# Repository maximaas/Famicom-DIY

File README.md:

# Famicom-DIY

My DIY work on Nintendo Famicom

## Controllers

### Convert FC controllers to adapt to 9-pin RS232 socket
The original FC controller have a 5-pin(1p) or 6-pin(2p) pin head plugged into the socket on main PCB board. Unlike its successors, the FC controller can not be replaced easily without opening the case.

One day a guy claimed that he had successfully designed and made a famiclone named "RGB-FC" which can output through RGBhv or VGA with splendid video quality. So I bought one.

RGB-FC provides two 9-pin controller connectors, can be used with a large number of "Subor" pads. But the pads are sucks, so I have to mod my original controllers to adapt with RGB-FC. 

First, I purchased several RS232 female connectors, then cut the pin head of the controller and started to wire them together.

The wiring method is showed above. The 2p controller has an additional mic wire than the 1p's. I don't know how to wire it so I left it lifted.

Solder the corresponding wires, and assemble the connector.

Enjoy!

## Reproductions

Refer to [https://maximaas.github.io/blog](https://maximaas.github.io/blog) for details.

*   kazzo_scripts: kazzo scripts for certain mappers that anago releases didn't provide or the original one doesn't work well.
*   MMC1 - SLROM.txt: wiring instruction for mmc1 slrom.
*   MMC5 - ETROM.txt: wiring instruction for mmc5 etrom.
*   Namcot-163.txt: wiring instruction for Namcot-163 board.
*   Taito X1-005.txt: wiring instruction for Taito X1-005 board.

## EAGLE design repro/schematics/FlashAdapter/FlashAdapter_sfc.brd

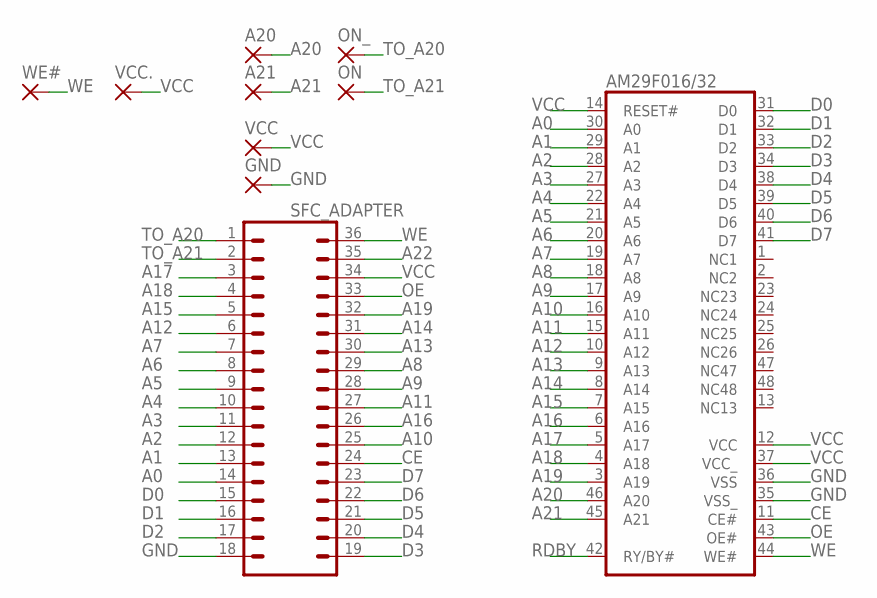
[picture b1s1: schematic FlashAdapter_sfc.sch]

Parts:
A20, A21: SMD2; SMD1,27-2,54
AM29F016/32: AM29F016; TSOP48
GND: SMD2; SMD1,27-2,54
ON: SMD2; SMD1,27-2,54
ON_: SMD2; SMD1,27-2,54
SFC_ADAPTER: DIP36PTH; DIP36
VCC, VCC.: SMD2; SMD1,27-2,54
WE#: SMD2; SMD1,27-2,54

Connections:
A0: AM29F016/32.30 (A0), SFC_ADAPTER.14
A1: AM29F016/32.29 (A1), SFC_ADAPTER.13
A2: AM29F016/32.28 (A2), SFC_ADAPTER.12
A3: AM29F016/32.27 (A3), SFC_ADAPTER.11
A4: AM29F016/32.22 (A4), SFC_ADAPTER.10
A5: AM29F016/32.21 (A5), SFC_ADAPTER.9
A6: AM29F016/32.20 (A6), SFC_ADAPTER.8
A7: AM29F016/32.19 (A7), SFC_ADAPTER.7
A8: AM29F016/32.18 (A8), SFC_ADAPTER.29
A9: AM29F016/32.17 (A9), SFC_ADAPTER.28
A10: AM29F016/32.16 (A10), SFC_ADAPTER.25
A11: AM29F016/32.15 (A11), SFC_ADAPTER.27
A12: AM29F016/32.10 (A12), SFC_ADAPTER.6
A13: AM29F016/32.9 (A13), SFC_ADAPTER.30
A14: AM29F016/32.8 (A14), SFC_ADAPTER.31
A15: AM29F016/32.7 (A15), SFC_ADAPTER.5
A16: AM29F016/32.6 (A16), SFC_ADAPTER.26
A17: AM29F016/32.5 (A17), SFC_ADAPTER.3
A18: AM29F016/32.4 (A18), SFC_ADAPTER.4
A19: AM29F016/32.3 (A19), SFC_ADAPTER.32
A20: A20.1, AM29F016/32.46 (A20)
A21: A21.1, AM29F016/32.45 (A21)
A22: SFC_ADAPTER.35
CE: AM29F016/32.11 (CE#), SFC_ADAPTER.24
D0: AM29F016/32.31 (D0), SFC_ADAPTER.15
D1: AM29F016/32.32 (D1), SFC_ADAPTER.16
D2: AM29F016/32.33 (D2), SFC_ADAPTER.17
D3: AM29F016/32.34 (D3), SFC_ADAPTER.19
D4: AM29F016/32.38 (D4), SFC_ADAPTER.20
D5: AM29F016/32.39 (D5), SFC_ADAPTER.21
D6: AM29F016/32.40 (D6), SFC_ADAPTER.22
D7: AM29F016/32.41 (D7), SFC_ADAPTER.23
GND: AM29F016/32.35 (VSS_), AM29F016/32.36 (VSS), GND.1, SFC_ADAPTER.18
OE: AM29F016/32.43 (OE#), SFC_ADAPTER.33
RDBY: AM29F016/32.42 (RY/BY#)
TO_A20: ON_.1, SFC_ADAPTER.1
TO_A21: ON.1, SFC_ADAPTER.2
VCC: AM29F016/32.12 (VCC), AM29F016/32.14 (RESET#), AM29F016/32.37 (VCC_), SFC_ADAPTER.34, VCC.1, VCC..1
WE: AM29F016/32.44 (WE#), SFC_ADAPTER.36, WE#.1

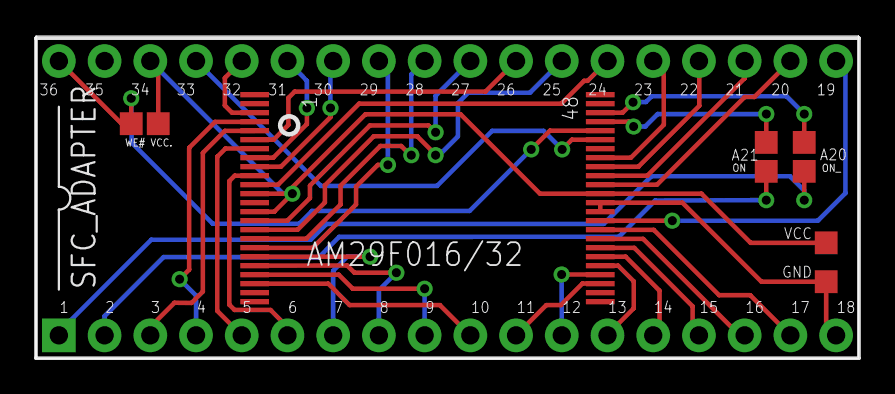
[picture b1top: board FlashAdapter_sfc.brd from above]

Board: 2 copper layers, 45.7 x 17.9 mm, 10 parts (0 on the bottom side), 37 nets.

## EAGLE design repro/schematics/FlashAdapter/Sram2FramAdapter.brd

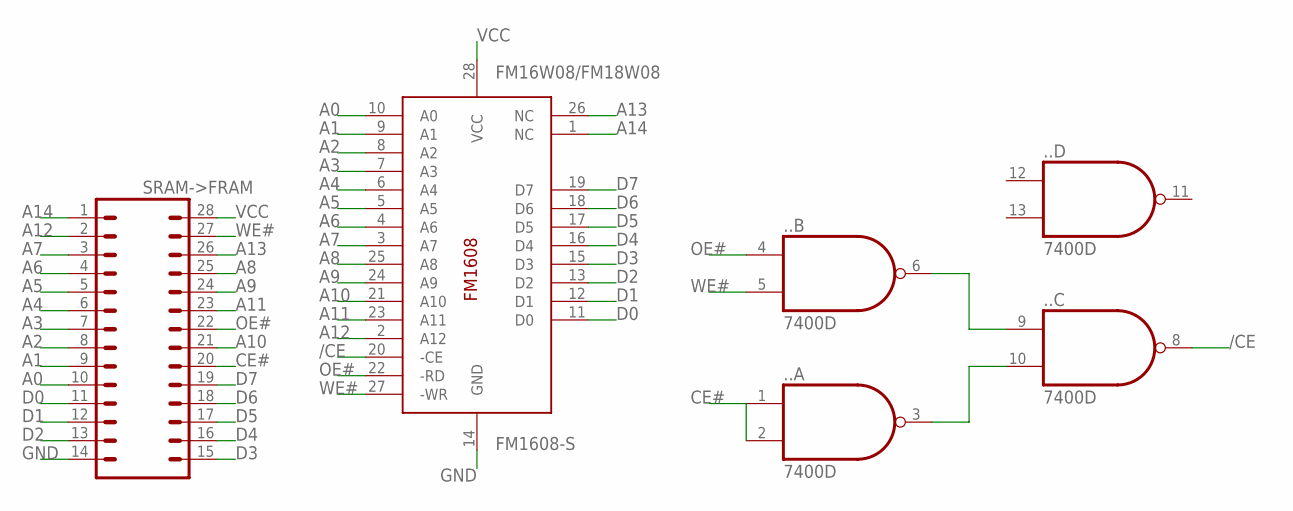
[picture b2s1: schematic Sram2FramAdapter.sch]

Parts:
..: 7400D; SO14
FM16W08/FM18W08: FM1608-S; SO-28W
SRAM->FRAM: DIP28PTH; DIP28

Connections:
/CE: ...8 (O), FM16W08/FM18W08.20 (-CE)
A0: FM16W08/FM18W08.10 (A0), SRAM->FRAM.10
A1: FM16W08/FM18W08.9 (A1), SRAM->FRAM.9
A2: FM16W08/FM18W08.8 (A2), SRAM->FRAM.8
A3: FM16W08/FM18W08.7 (A3), SRAM->FRAM.7
A4: FM16W08/FM18W08.6 (A4), SRAM->FRAM.6
A5: FM16W08/FM18W08.5 (A5), SRAM->FRAM.5
A6: FM16W08/FM18W08.4 (A6), SRAM->FRAM.4
A7: FM16W08/FM18W08.3 (A7), SRAM->FRAM.3
A8: FM16W08/FM18W08.25 (A8), SRAM->FRAM.25
A9: FM16W08/FM18W08.24 (A9), SRAM->FRAM.24
A10: FM16W08/FM18W08.21 (A10), SRAM->FRAM.21
A11: FM16W08/FM18W08.23 (A11), SRAM->FRAM.23
A12: FM16W08/FM18W08.2 (A12), SRAM->FRAM.2
A13: FM16W08/FM18W08.26 (NC), SRAM->FRAM.26
A14: FM16W08/FM18W08.1 (NC), SRAM->FRAM.1
CE#: ...1 (I0), ...2 (I1), SRAM->FRAM.20
D0: FM16W08/FM18W08.11 (D0), SRAM->FRAM.11
D1: FM16W08/FM18W08.12 (D1), SRAM->FRAM.12
D2: FM16W08/FM18W08.13 (D2), SRAM->FRAM.13
D3: FM16W08/FM18W08.15 (D3), SRAM->FRAM.15
D4: FM16W08/FM18W08.16 (D4), SRAM->FRAM.16
D5: FM16W08/FM18W08.17 (D5), SRAM->FRAM.17
D6: FM16W08/FM18W08.18 (D6), SRAM->FRAM.18
D7: FM16W08/FM18W08.19 (D7), SRAM->FRAM.19
GND: ...7 (GND), FM16W08/FM18W08.14 (GND), SRAM->FRAM.14
unnamed: ...6 (O), ...9 (I0)
unnamed: ...3 (O), ...10 (I1)
OE#: ...4 (I0), FM16W08/FM18W08.22 (-RD), SRAM->FRAM.22
VCC: ...14 (VCC), FM16W08/FM18W08.28 (VCC), SRAM->FRAM.28
WE#: ...5 (I1), FM16W08/FM18W08.27 (-WR), SRAM->FRAM.27

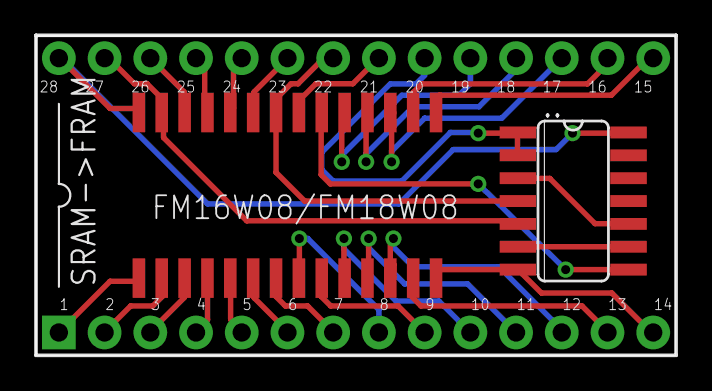
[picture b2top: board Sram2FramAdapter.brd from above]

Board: 2 copper layers, 35.5 x 17.7 mm, 3 parts (0 on the bottom side), 31 nets.

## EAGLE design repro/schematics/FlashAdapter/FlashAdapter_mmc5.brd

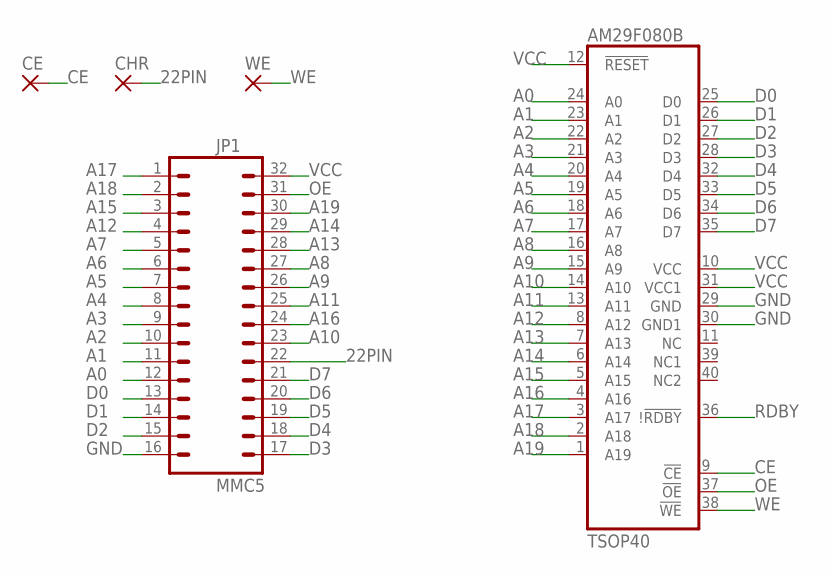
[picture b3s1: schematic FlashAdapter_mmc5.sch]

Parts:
AM29F080B: TSOP40
CE: SMD2; SMD1,27-2,54
CHR: SMD2; SMD1,27-2,54
JP1: MMC5; DIP32
WE: SMD2; SMD1,27-2,54

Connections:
22PIN: CHR.1, JP1.22
A0: AM29F080B.24 (A0), JP1.12
A1: AM29F080B.23 (A1), JP1.11
A2: AM29F080B.22 (A2), JP1.10
A3: AM29F080B.21 (A3), JP1.9
A4: AM29F080B.20 (A4), JP1.8
A5: AM29F080B.19 (A5), JP1.7
A6: AM29F080B.18 (A6), JP1.6
A7: AM29F080B.17 (A7), JP1.5
A8: AM29F080B.16 (A8), JP1.27
A9: AM29F080B.15 (A9), JP1.26
A10: AM29F080B.14 (A10), JP1.23
A11: AM29F080B.13 (A11), JP1.25
A12: AM29F080B.8 (A12), JP1.4
A13: AM29F080B.7 (A13), JP1.28
A14: AM29F080B.6 (A14), JP1.29
A15: AM29F080B.5 (A15), JP1.3
A16: AM29F080B.4 (A16), JP1.24
A17: AM29F080B.3 (A17), JP1.1
A18: AM29F080B.2 (A18), JP1.2
A19: AM29F080B.1 (A19), JP1.30
CE: AM29F080B.9 (!CE), CE.1
D0: AM29F080B.25 (D0), JP1.13
D1: AM29F080B.26 (D1), JP1.14
D2: AM29F080B.27 (D2), JP1.15
D3: AM29F080B.28 (D3), JP1.17
D4: AM29F080B.32 (D4), JP1.18
D5: AM29F080B.33 (D5), JP1.19
D6: AM29F080B.34 (D6), JP1.20
D7: AM29F080B.35 (D7), JP1.21
GND: AM29F080B.29 (GND), AM29F080B.30 (GND1), JP1.16
OE: AM29F080B.37 (!OE), JP1.31
RDBY: AM29F080B.36 (!!RDBY)
VCC: AM29F080B.10 (VCC), AM29F080B.12 (!RESET), AM29F080B.31 (VCC1), JP1.32
WE: AM29F080B.38 (!WE), WE.1

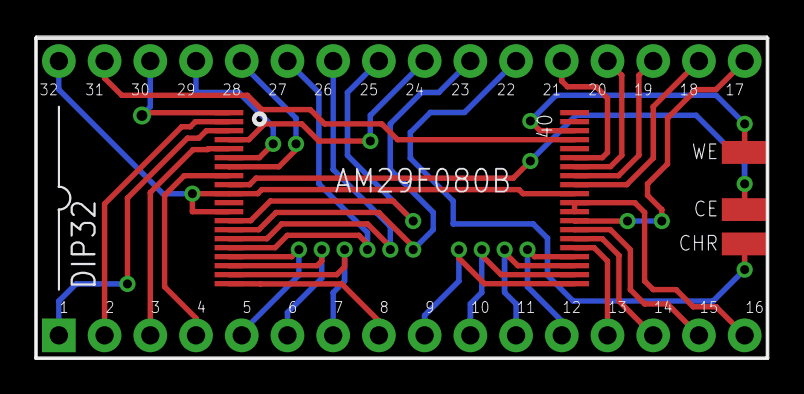
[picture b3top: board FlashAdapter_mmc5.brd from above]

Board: 2 copper layers, 40.6 x 17.9 mm, 5 parts (0 on the bottom side), 34 nets.

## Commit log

2017-08-15 upload
2021-02-20 add sfc repro files

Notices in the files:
parts and their libraries:
Adapter_DIP32: Licensing: Creative Commons ShareAlike 4.0 International - https://creativecommons.org/licenses/by-sa/4.0
